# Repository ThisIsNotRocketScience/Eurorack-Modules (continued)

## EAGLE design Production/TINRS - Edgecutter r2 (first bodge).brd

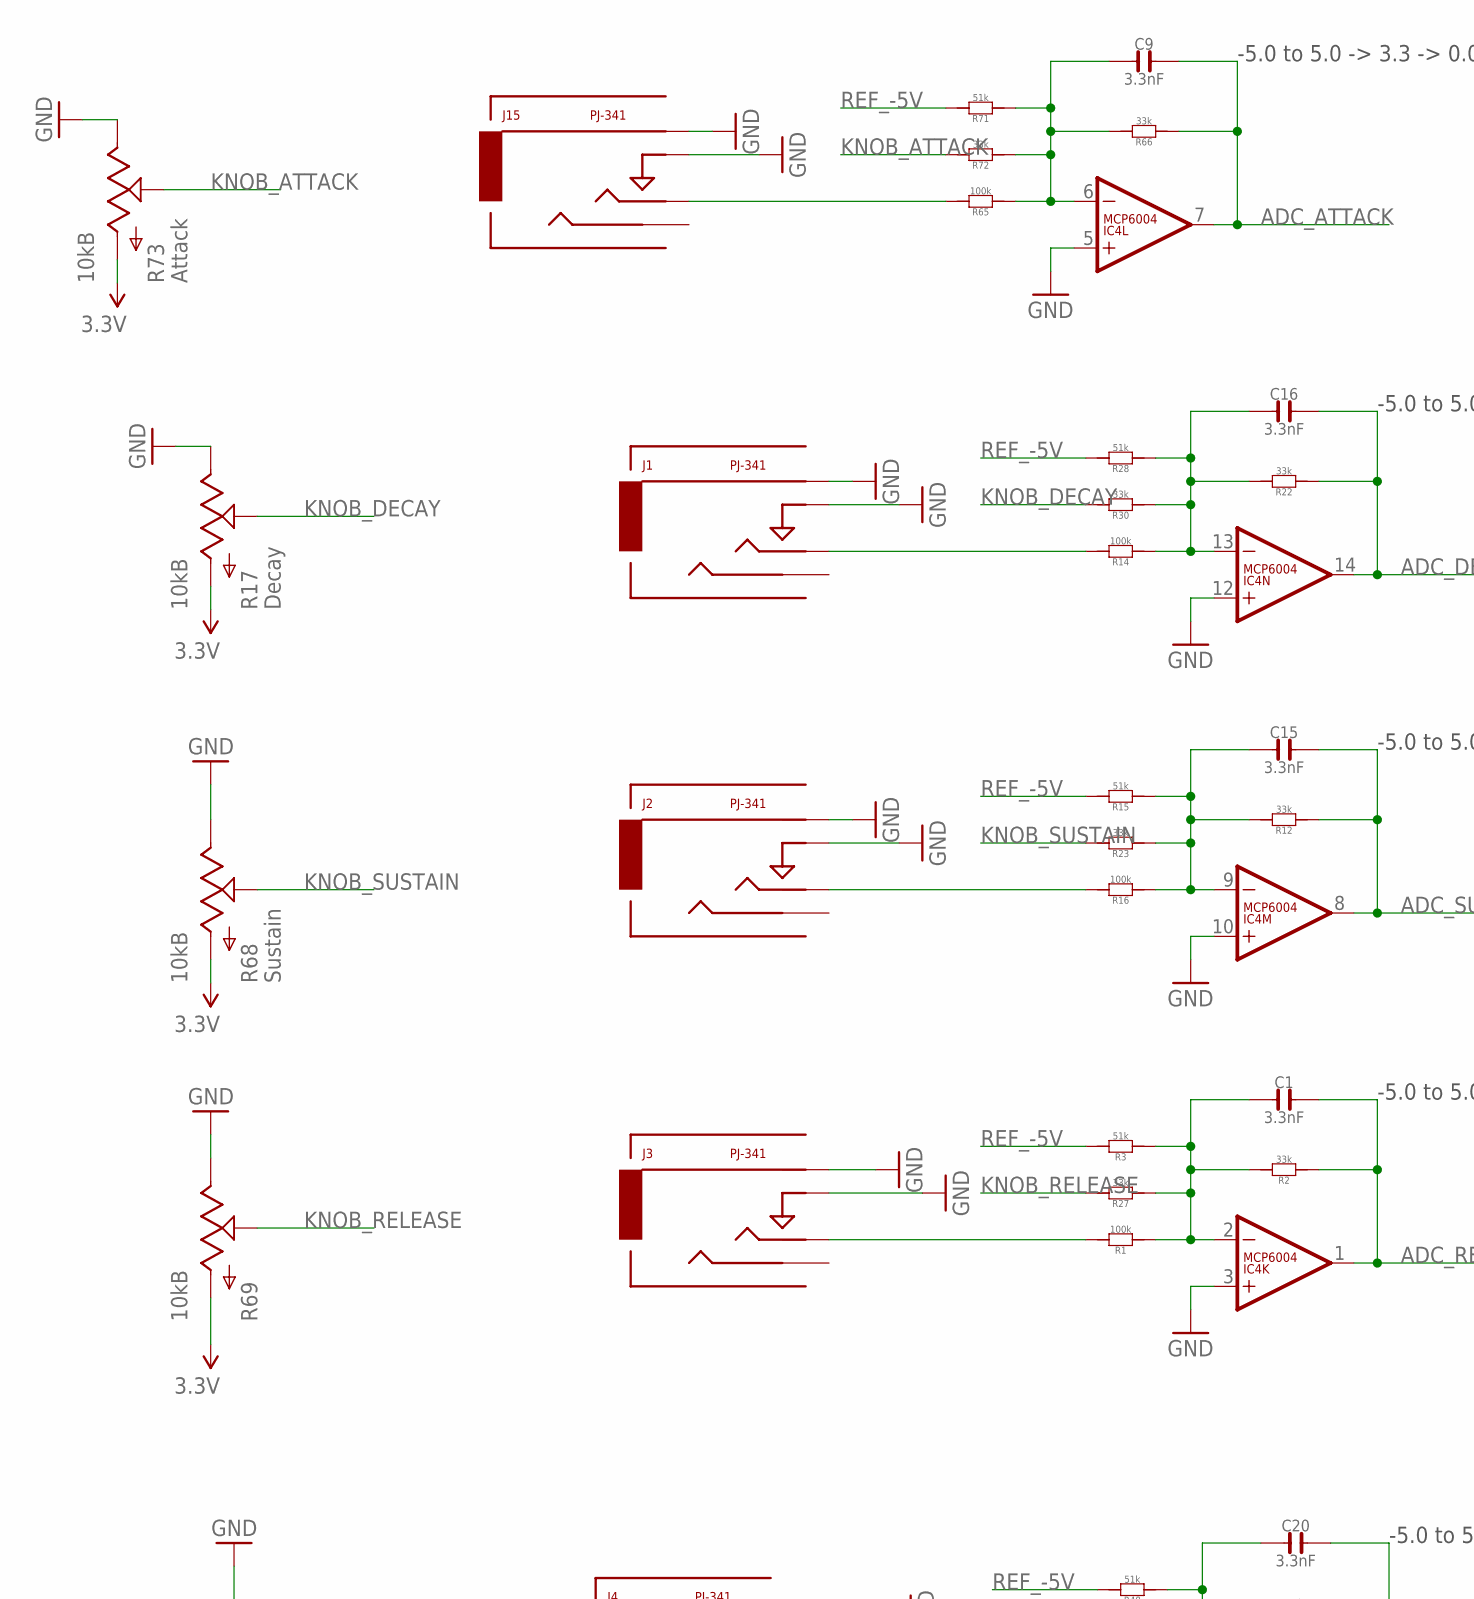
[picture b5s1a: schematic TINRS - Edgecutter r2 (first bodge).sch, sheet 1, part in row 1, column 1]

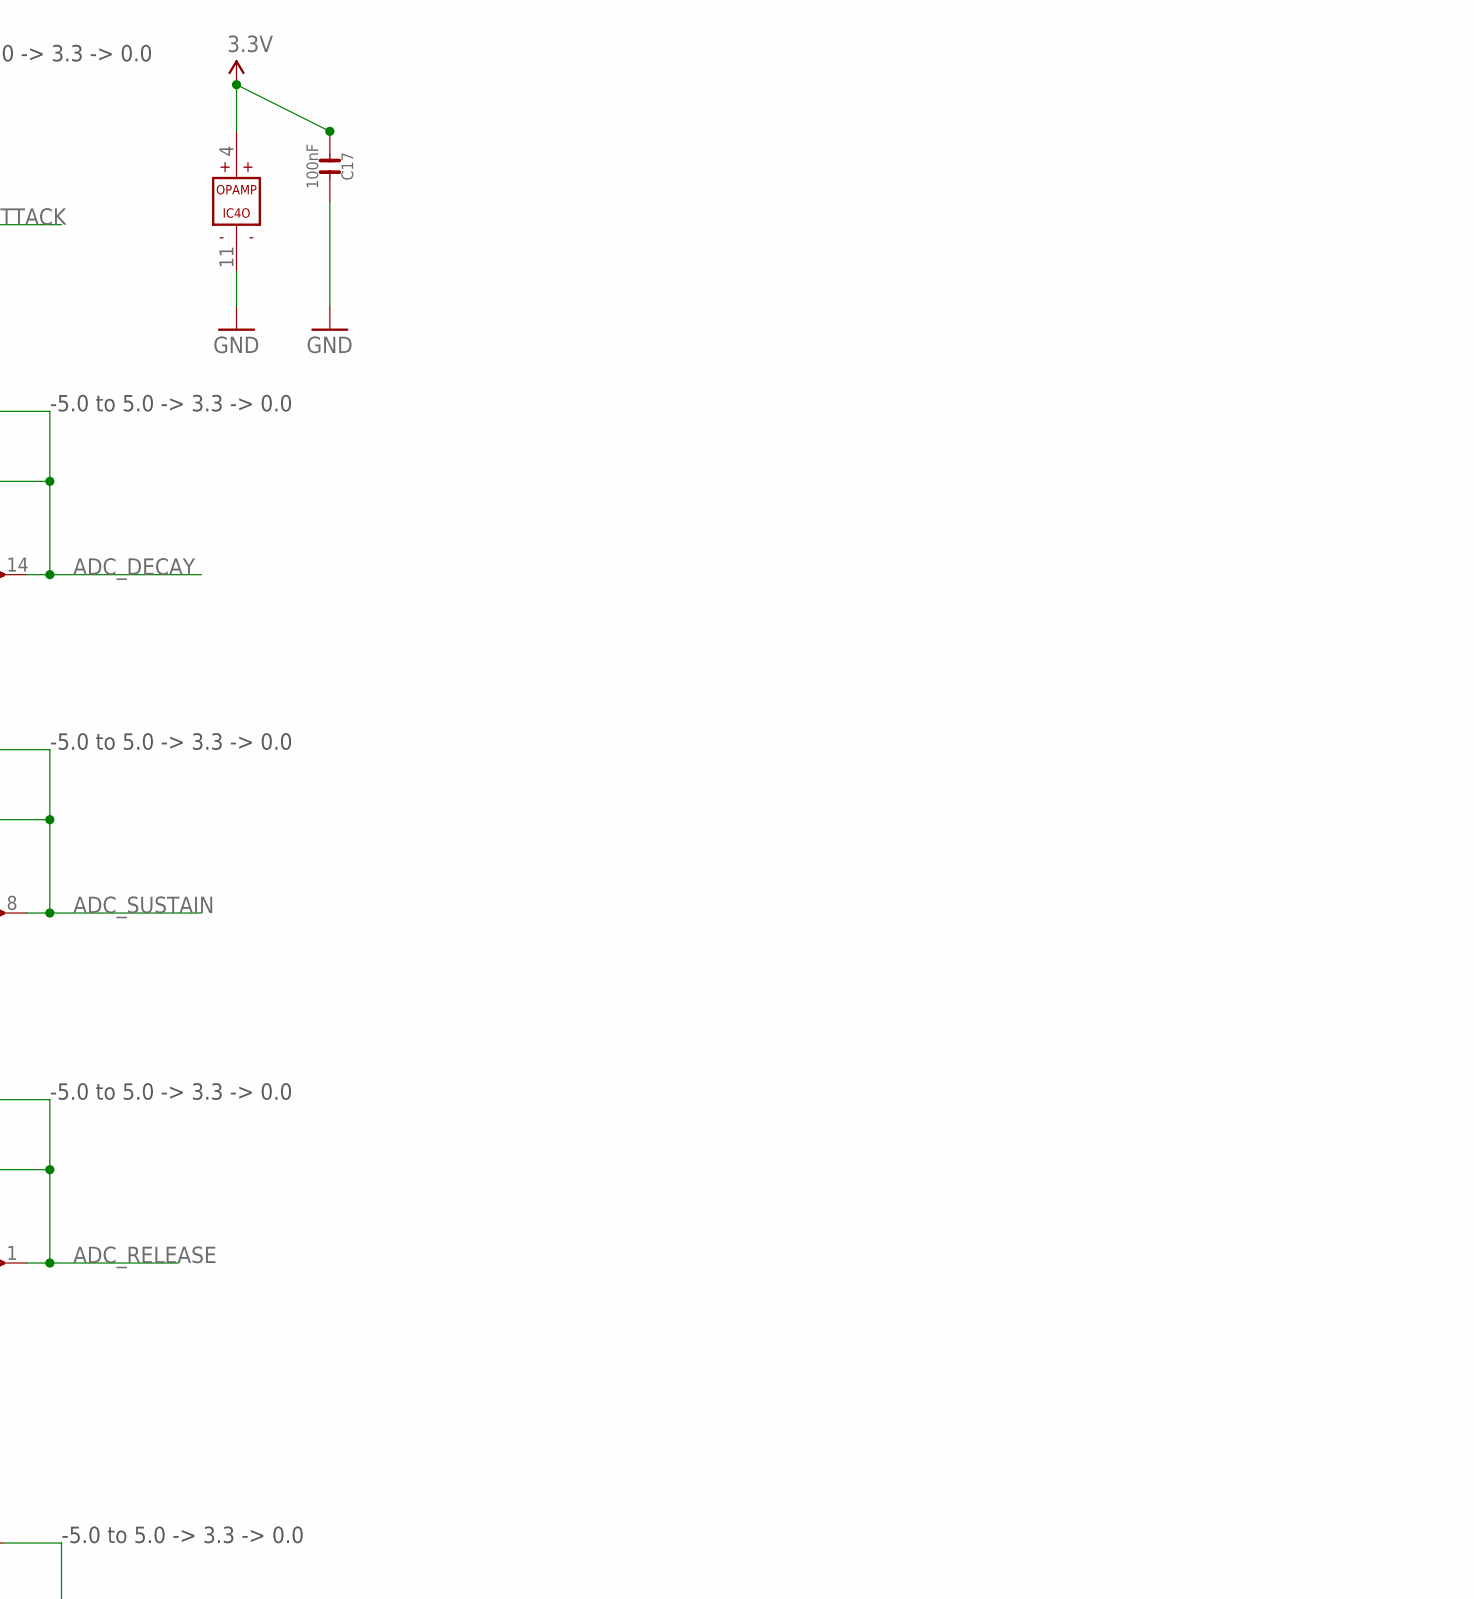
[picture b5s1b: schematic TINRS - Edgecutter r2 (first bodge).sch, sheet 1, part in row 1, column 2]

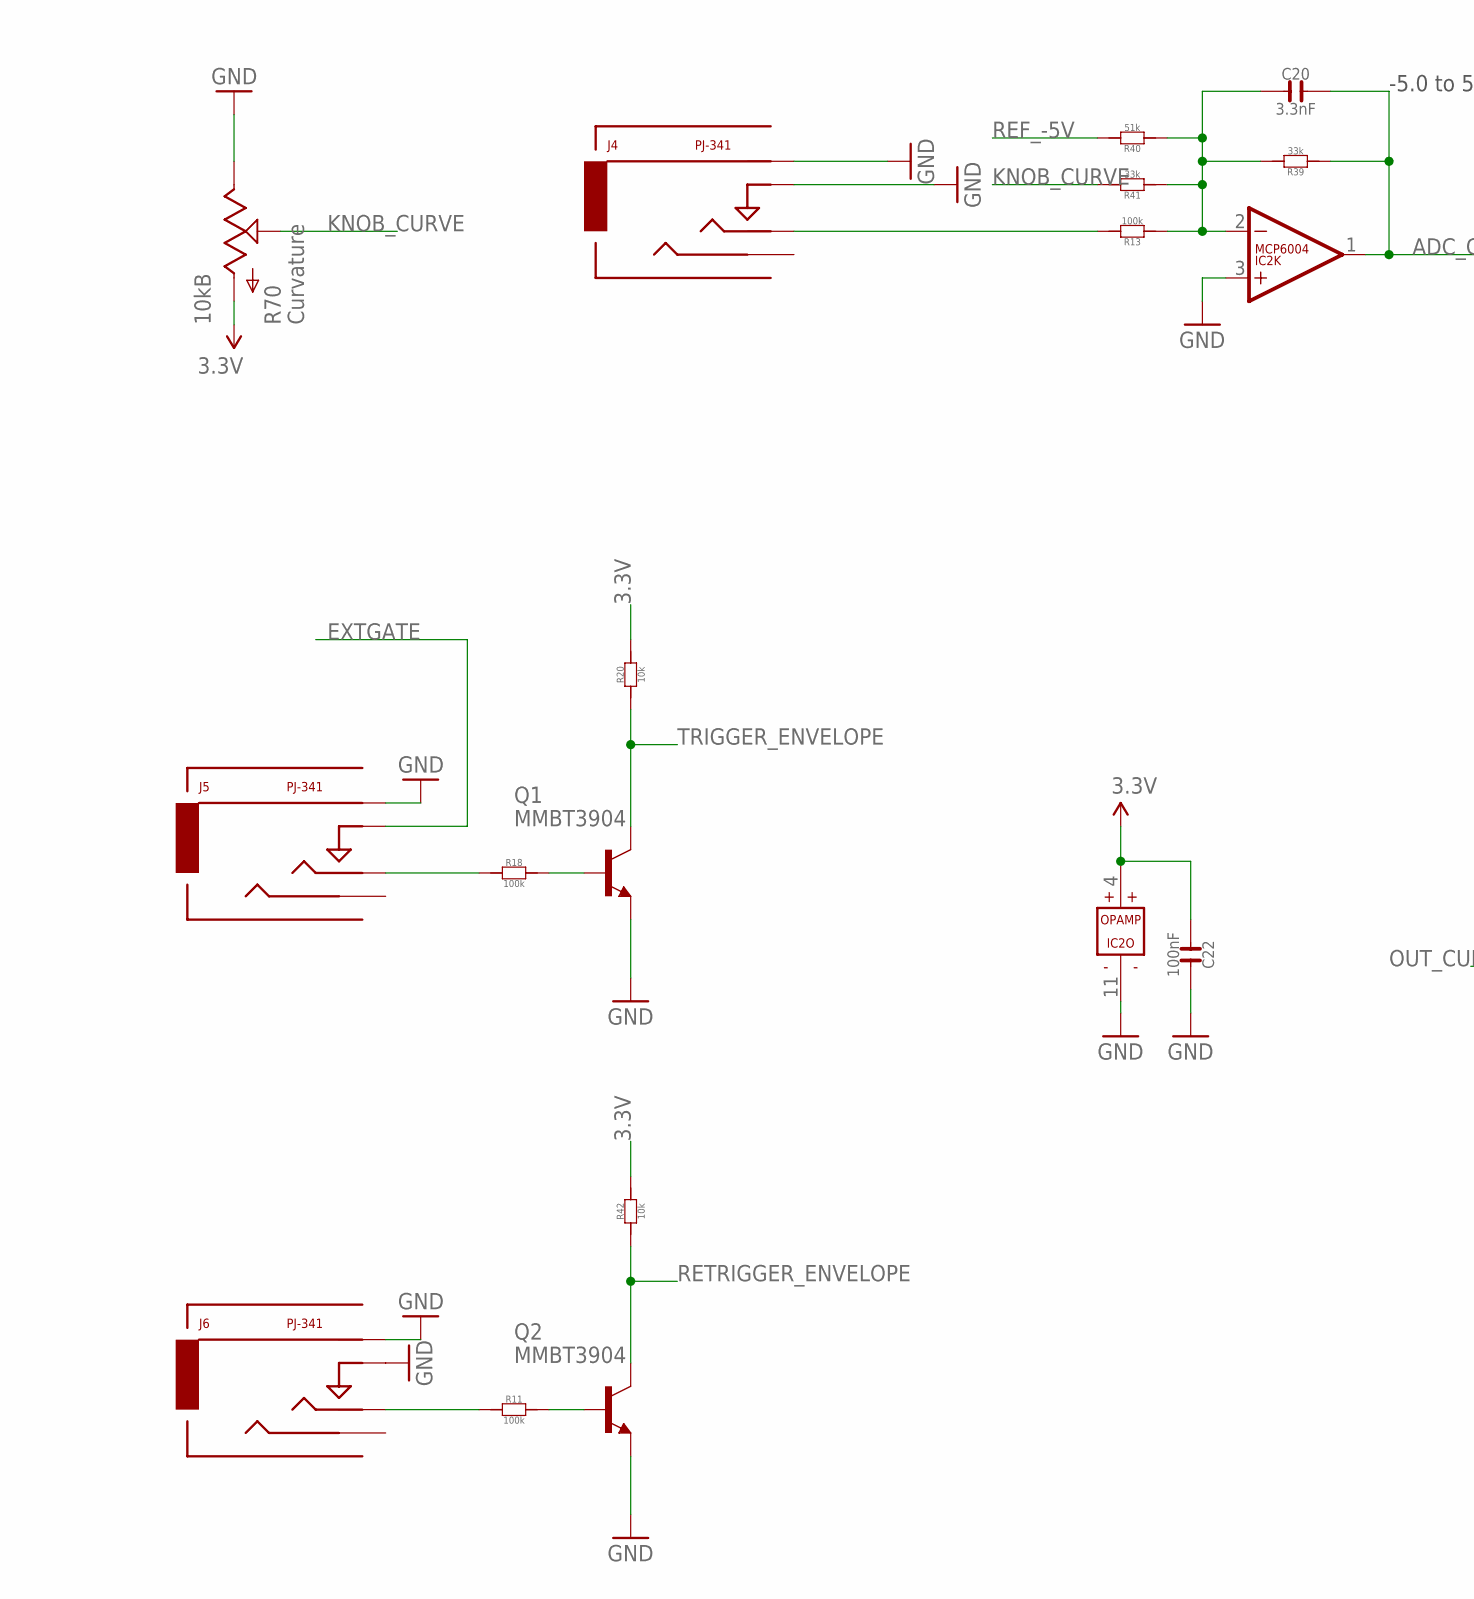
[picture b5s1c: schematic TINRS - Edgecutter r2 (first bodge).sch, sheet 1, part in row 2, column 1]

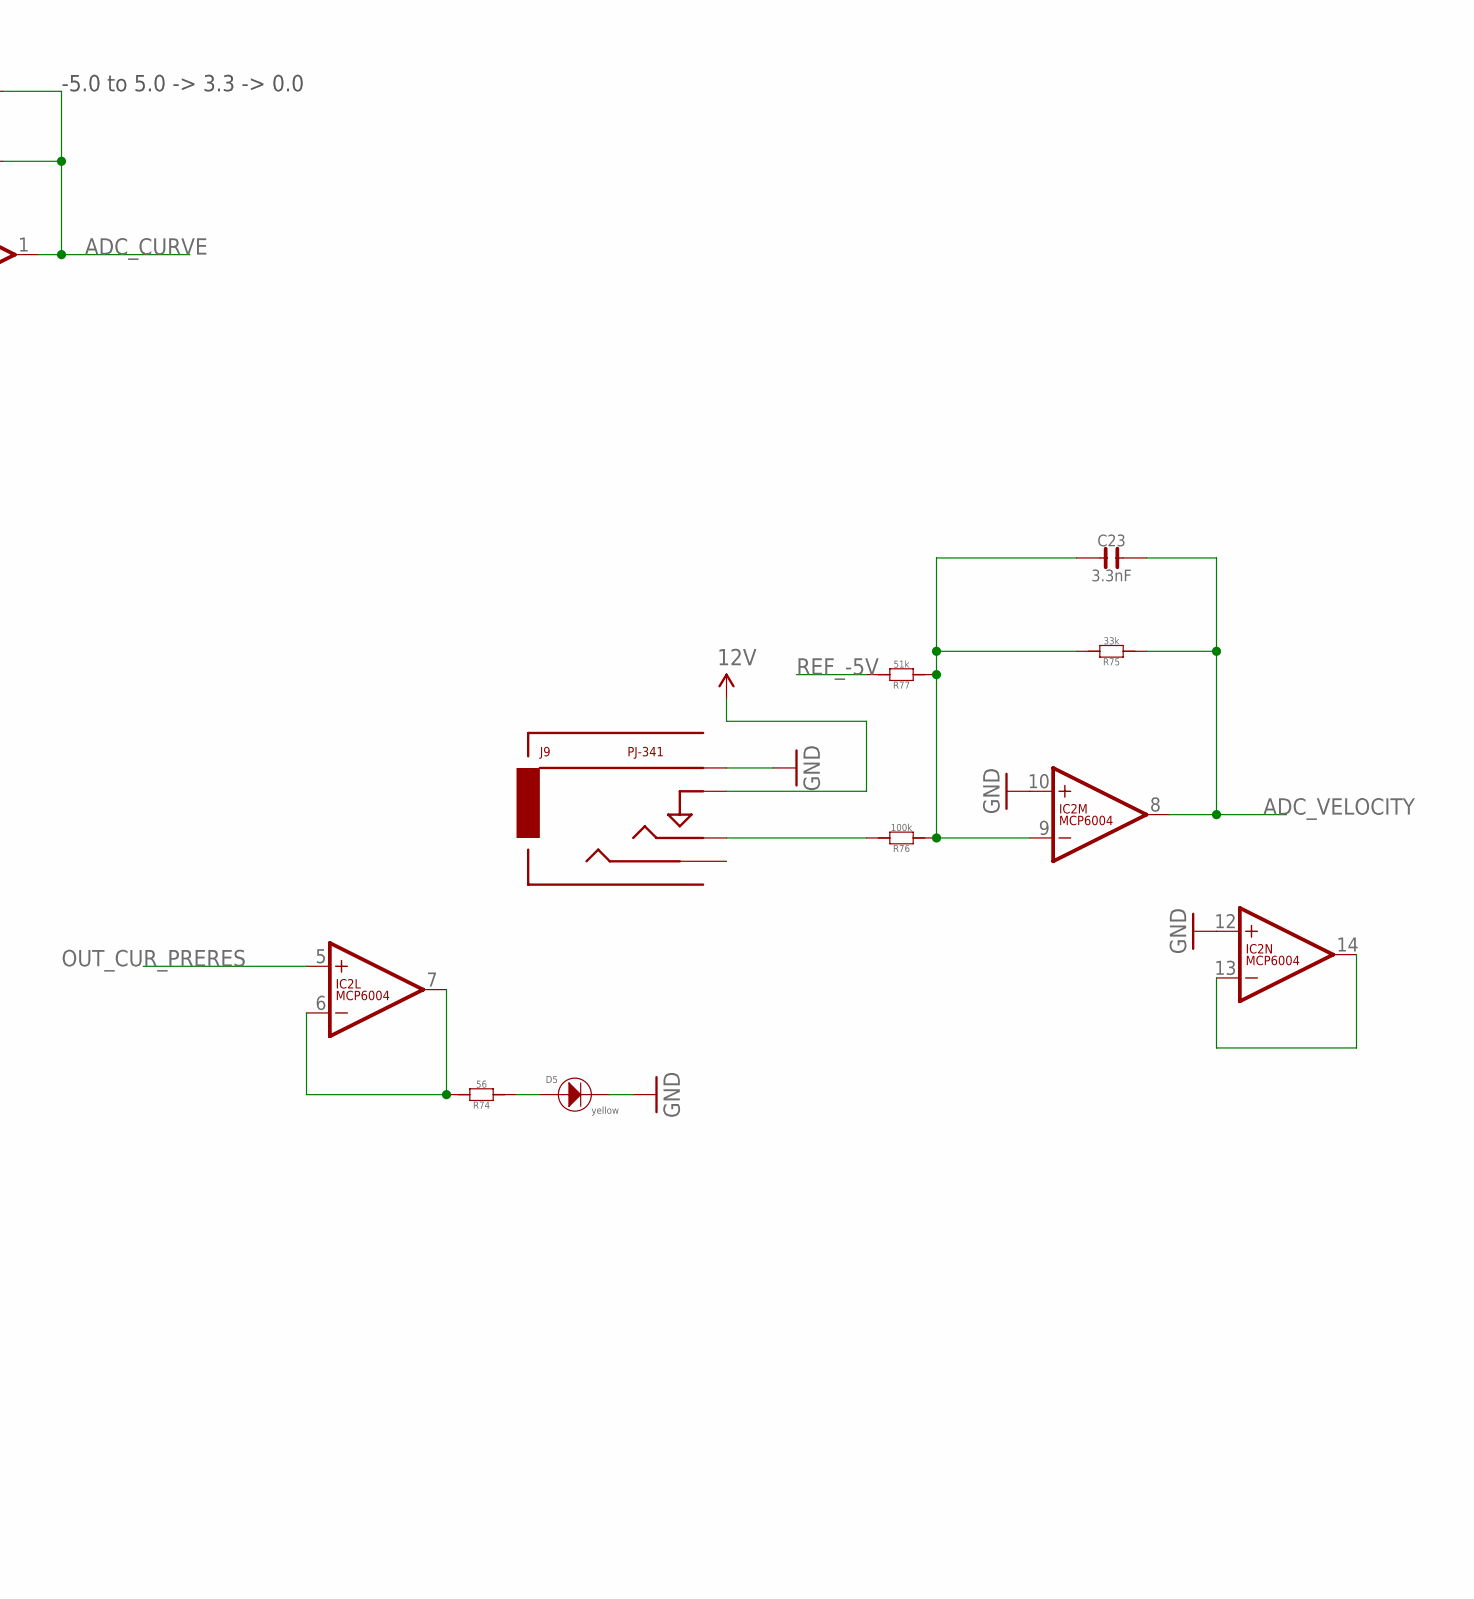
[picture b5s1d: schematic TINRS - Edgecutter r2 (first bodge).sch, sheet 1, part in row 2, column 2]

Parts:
C1, C9, C15, C16, C20, C23: 3.3nF; C0603
C17, C22: 100nF; C0603; MPN MC0603F104Z160CT
D5: yellow; 3MMLED
IC2, IC4: MCP6004; SO14; MPN MCP6004-I/SL.
J1, J2, J3, J4, J5, J6, J9, J15: PJ-341; 3.5MM-JACK-SWITCH-13MM-INPUT
Q1, Q2: MMBT3904; SOT23-BEC; MPN PMBT3904,215
R1, R11, R13, R14, R16, R18, R65, R76: 100k; R0603
R2, R12, R22, R23, R27, R30, R39, R41, R66, R72, R75: 33k; R0603
R3, R15, R28, R40, R71, R77: 51k; R0603
R17, R68, R69, R70, R73: 10kB; OG-POTS_ALPS_POT_VERTICAL
R20, R42: 10k; R0603
R74: 56; R0603

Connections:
3.3V: C17.1, C22.1, IC2.4 (V+), IC4.4 (V+), R17.P$3 (A), R20.2, R42.2, R68.P$3 (A), R69.P$3 (A), R70.P$3 (A), R73.P$3 (A); also elsewhere on the board
12V: J9.SWITCH@3 (SWITCH); also elsewhere on the board
ADC_ATTACK: C9.2, IC4.7 (OUT), R66.1; also elsewhere on the board
ADC_CURVE: C20.2, IC2.1 (OUT), R39.1; also elsewhere on the board
ADC_DECAY: C16.2, IC4.14 (OUT), R22.1; also elsewhere on the board
ADC_RELEASE: C1.2, IC4.1 (OUT), R2.1; also elsewhere on the board
ADC_SUSTAIN: C15.2, IC4.8 (OUT), R12.1; also elsewhere on the board
ADC_VELOCITY: C23.2, IC2.8 (OUT), R75.1; also elsewhere on the board
EXTGATE: J5.SWITCH@3 (SWITCH); also elsewhere on the board
GND: C17.2, C22.2, D5.-, IC2.3 (+IN), IC2.10 (+IN), IC2.11 (V-), IC2.12 (+IN), IC4.3 (+IN), IC4.5 (+IN), IC4.10 (+IN), IC4.11 (V-), IC4.12 (+IN), J1.RING@3 (RING), J1.SWITCH@3 (SWITCH), J2.RING@3 (RING), J2.SWITCH@3 (SWITCH), J3.RING@3 (RING), J3.SWITCH@3 (SWITCH), J4.RING@3 (RING), J4.SWITCH@3 (SWITCH), J5.RING@3 (RING), J6.RING@3 (RING), J6.SWITCH@3 (SWITCH), J9.RING@3 (RING), J15.RING@3 (RING), J15.SWITCH@3 (SWITCH), Q1.E, Q2.E, R17.P$1 (E), R68.P$1 (E), R69.P$1 (E), R70.P$1 (E), R73.P$1 (E); also elsewhere on the board
KNOB_ATTACK: R72.2, R73.P$2 (S)
KNOB_CURVE: R41.2, R70.P$2 (S)
KNOB_DECAY: R17.P$2 (S), R30.2
KNOB_RELEASE: R27.2, R69.P$2 (S)
KNOB_SUSTAIN: R23.2, R68.P$2 (S)
unnamed: J2.TIP@3 (TIP), R16.2
unnamed: C15.1, IC4.9 (-IN), R12.2, R15.1, R16.1, R23.1
unnamed: J3.TIP@3 (TIP), R1.2
unnamed: C1.1, IC4.2 (-IN), R1.1, R2.2, R3.1, R27.1
unnamed: J15.TIP@3 (TIP), R65.2
unnamed: J4.TIP@3 (TIP), R13.2
unnamed: Q1.B, R18.2
unnamed: J5.TIP@3 (TIP), R18.1
unnamed: IC2.6 (-IN), IC2.7 (OUT), R74.2
unnamed: C9.1, IC4.6 (-IN), R65.1, R66.2, R71.1, R72.1
unnamed: IC2.13 (-IN), IC2.14 (OUT)
unnamed: J1.TIP@3 (TIP), R14.2
unnamed: C16.1, IC4.13 (-IN), R14.1, R22.2, R28.1, R30.1
unnamed: Q2.B, R11.2
unnamed: C20.1, IC2.2 (-IN), R13.1, R39.2, R40.1, R41.1
unnamed: J6.TIP@3 (TIP), R11.1
unnamed: C23.1, IC2.9 (-IN), R75.2, R76.1, R77.1
unnamed: D5.+, R74.1
unnamed: J9.TIP@3 (TIP), R76.2
OUT_CUR_PRERES: IC2.5 (+IN); also elsewhere on the board
REF_-5V: R3.2, R15.2, R28.2, R40.2, R71.2, R77.2; also elsewhere on the board
RETRIGGER_ENVELOPE: Q2.C, R42.1; also elsewhere on the board
TRIGGER_ENVELOPE: Q1.C, R20.1; also elsewhere on the board

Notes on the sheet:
-5.0 to 5.0 -> 3.3 -> 0.0

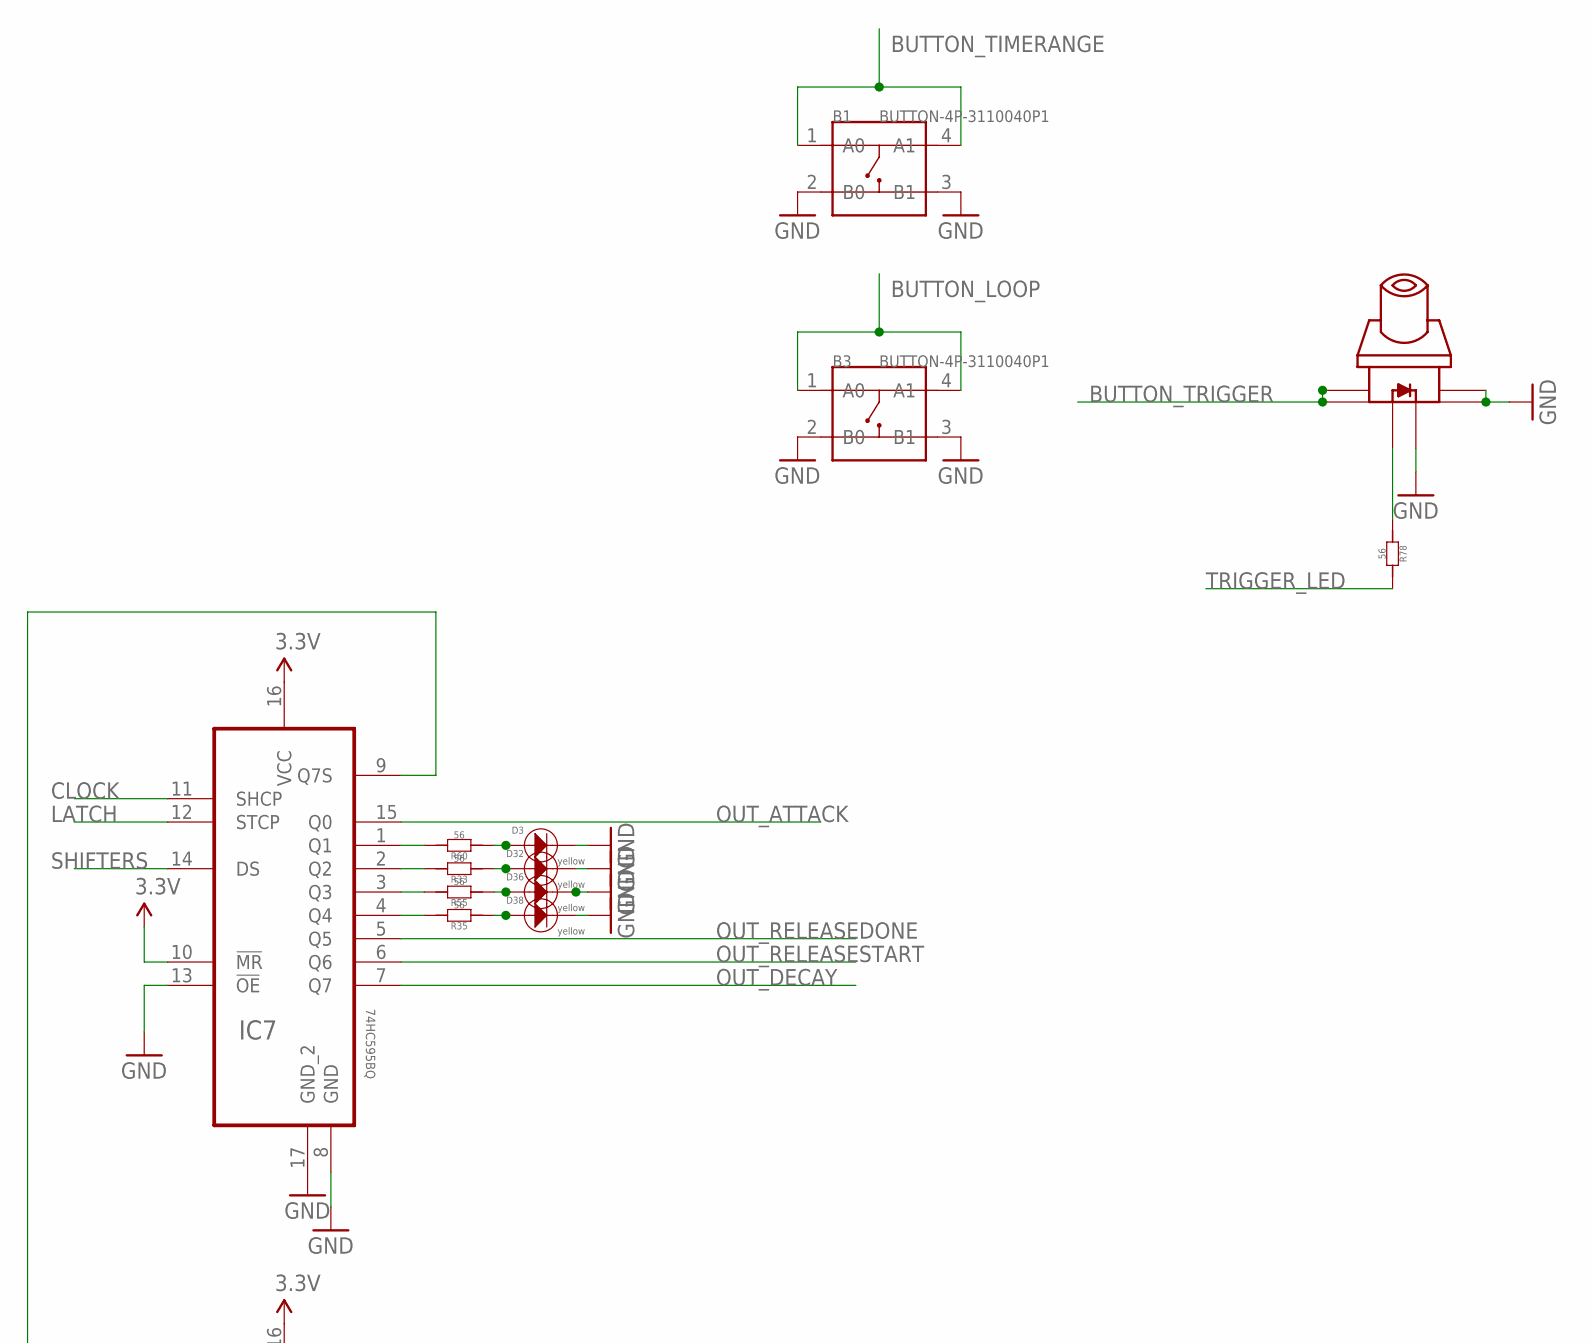
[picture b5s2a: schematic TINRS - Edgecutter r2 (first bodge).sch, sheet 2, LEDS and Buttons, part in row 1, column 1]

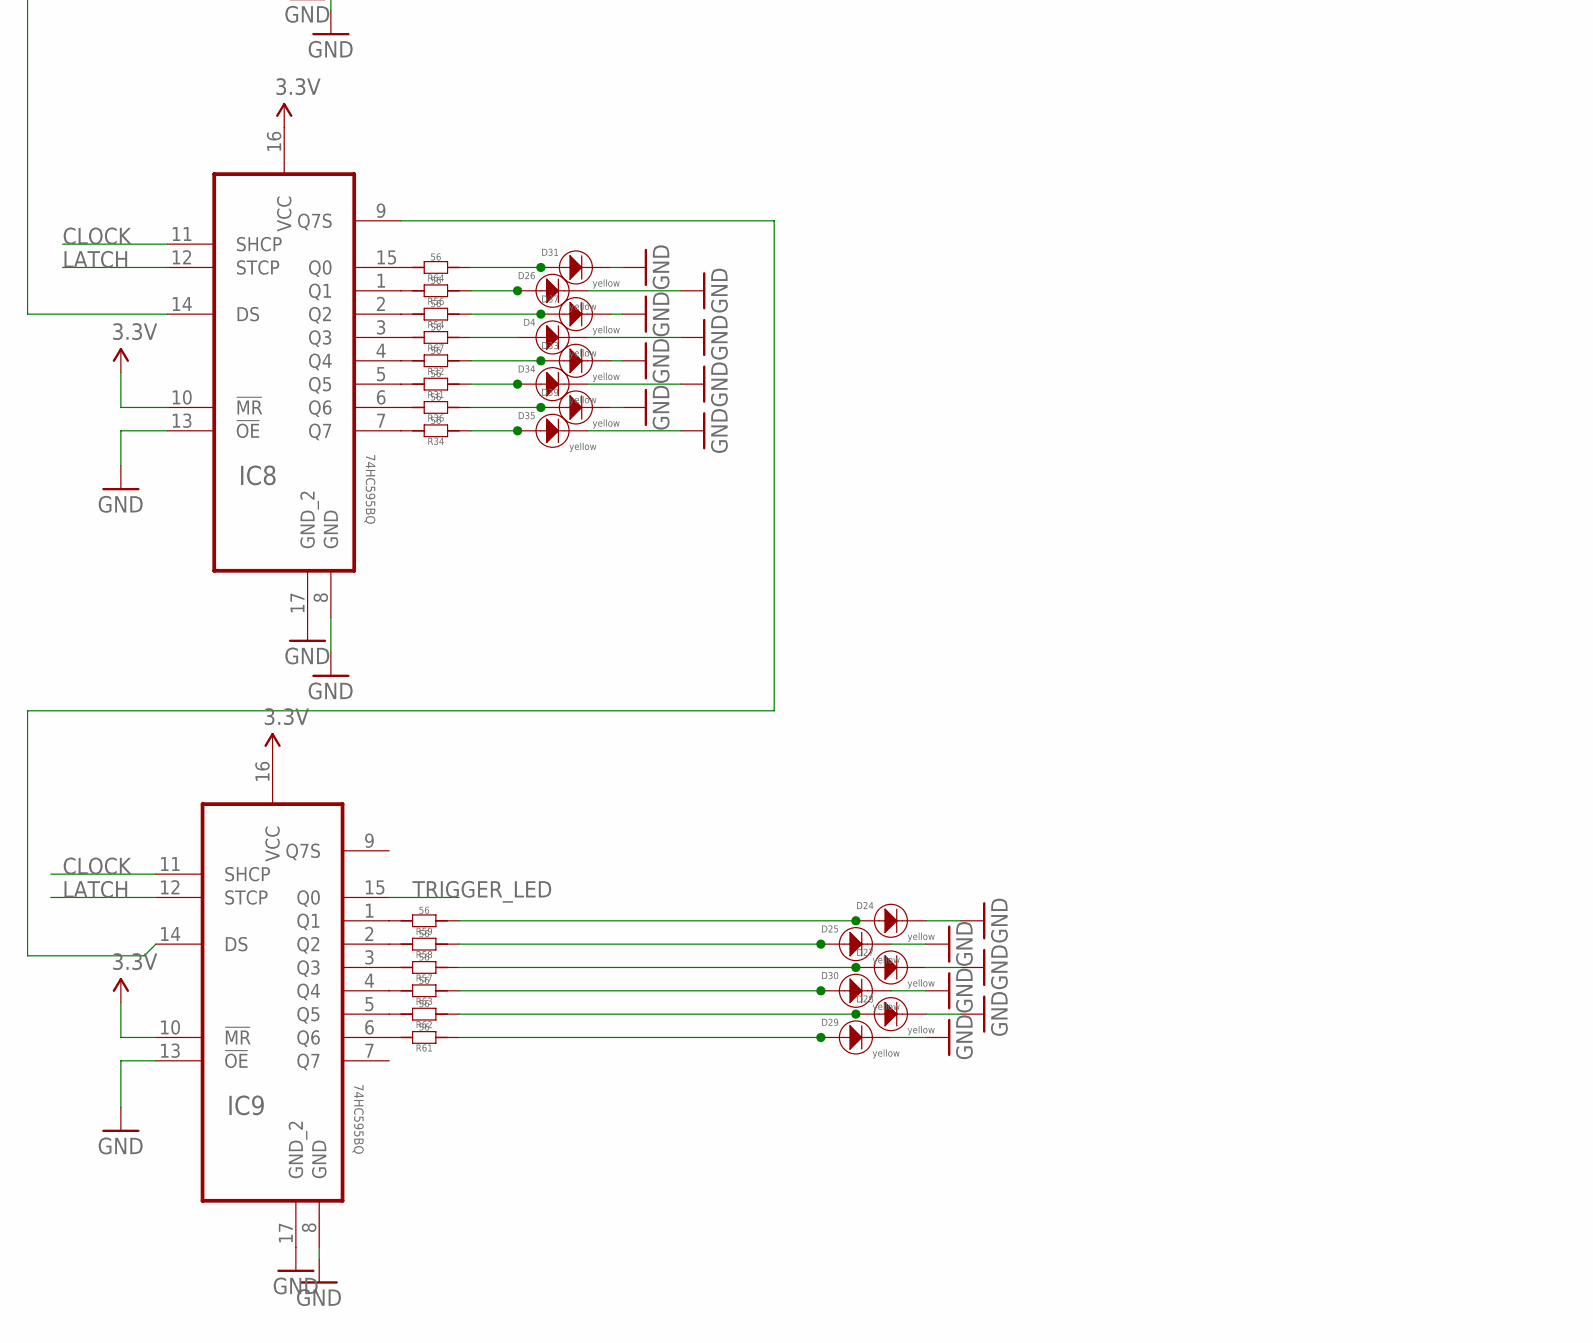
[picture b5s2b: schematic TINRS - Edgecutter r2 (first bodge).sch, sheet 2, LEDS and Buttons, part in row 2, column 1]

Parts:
B1, B3: BUTTON-4P-3110040P1; 4P-6.0X6.0X5.0H
D3, D4, D24, D25, D26, D27, D28, D29, D30, D31, D32, D33, D34, D35, D36, D37, D38, D39: yellow; 3MMLED
IC7, IC8, IC9: 74HC595BQ; QFN50P250X350X100-17N
R31, R32, R33, R34, R35, R36, R54, R55, R56, R57, R58, R59, R60, R61, R62, R63, R64, R67, R78: 56; R0603
U$2: SWITCH_W_LED_PB6149L-X-102YELLOW; PB6149L

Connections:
3.3V: IC7.10 (!MR), IC7.16 (VCC), IC8.10 (!MR), IC8.16 (VCC), IC9.10 (!MR), IC9.16 (VCC); also elsewhere on the board
BUTTON_LOOP: B3.1 (A0), B3.4 (A1); also elsewhere on the board
BUTTON_TIMERANGE: B1.1 (A0), B1.4 (A1); also elsewhere on the board
BUTTON_TRIGGER: U$2.1, U$2.2; also elsewhere on the board
CLOCK: IC7.11 (SHCP), IC8.11 (SHCP), IC9.11 (SHCP); also elsewhere on the board
GND: B1.2 (B0), B1.3 (B1), B3.2 (B0), B3.3 (B1), D3.-, D4.-, D24.-, D25.-, D26.-, D27.-, D28.-, D29.-, D30.-, D31.-, D32.-, D33.-, D34.-, D35.-, D36.-, D37.-, D38.-, D39.-, IC7.8 (GND), IC7.13 (!OE), IC7.17 (GND_2), IC8.8 (GND), IC8.13 (!OE), IC8.17 (GND_2), IC9.8 (GND), IC9.13 (!OE), IC9.17 (GND_2), U$2.3, U$2.4, U$2.LEDNEG (NEG); also elsewhere on the board
LATCH: IC7.12 (STCP), IC8.12 (STCP), IC9.12 (STCP); also elsewhere on the board
unnamed: R78.1, U$2.LEDPOS (POS)
unnamed: IC8.7 (Q7), R34.2
unnamed: IC8.15 (Q0), R64.2
unnamed: D28.+, R62.1
unnamed: D4.+, R67.1
unnamed: IC7.1 (Q1), R60.2
unnamed: D29.+, R61.1
unnamed: IC7.2 (Q2), R33.2
unnamed: IC7.3 (Q3), R55.2
unnamed: IC7.4 (Q4), R35.2
unnamed: IC8.1 (Q1), R56.2
unnamed: IC8.2 (Q2), R54.2
unnamed: IC8.3 (Q3), R67.2
unnamed: IC8.4 (Q4), R32.2
unnamed: IC8.5 (Q5), R31.2
unnamed: IC8.6 (Q6), R36.2
unnamed: IC9.1 (Q1), R59.2
unnamed: IC9.2 (Q2), R58.2
unnamed: D3.+, R60.1
unnamed: IC9.3 (Q3), R57.2
unnamed: IC9.4 (Q4), R63.2
unnamed: IC9.5 (Q5), R62.2
unnamed: IC9.6 (Q6), R61.2
unnamed: D27.+, R57.1
unnamed: D26.+, R56.1
unnamed: D25.+, R58.1
unnamed: D24.+, R59.1
unnamed: D30.+, R63.1
unnamed: D31.+, R64.1
unnamed: D32.+, R33.1
unnamed: D33.+, R32.1
unnamed: D34.+, R31.1
unnamed: D35.+, R34.1
unnamed: D36.+, R55.1
unnamed: D37.+, R54.1
unnamed: D38.+, R35.1
unnamed: D39.+, R36.1
OUT_ATTACK: IC7.15 (Q0); also elsewhere on the board
OUT_DECAY: IC7.7 (Q7); also elsewhere on the board
OUT_RELEASEDONE: IC7.5 (Q5); also elsewhere on the board
OUT_RELEASESTART: IC7.6 (Q6); also elsewhere on the board
SHIFTER1TO2: IC7.9 (Q7S), IC8.14 (DS)
SHIFTER2TO3: IC8.9 (Q7S), IC9.14 (DS)
SHIFTERS: IC7.14 (DS); also elsewhere on the board
TRIGGER_LED: IC9.15 (Q0), R78.2

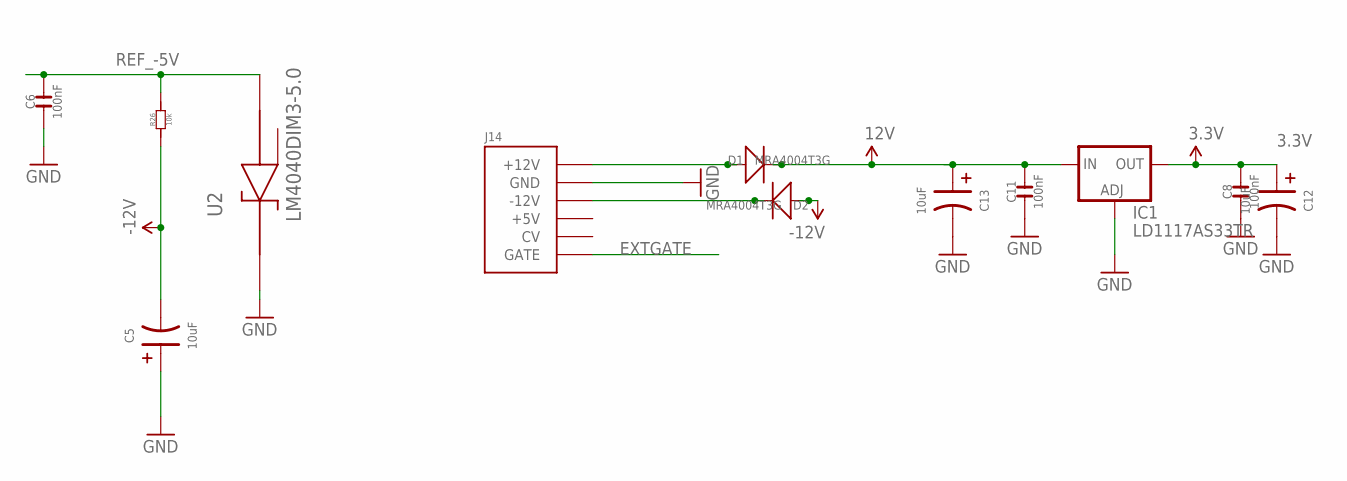
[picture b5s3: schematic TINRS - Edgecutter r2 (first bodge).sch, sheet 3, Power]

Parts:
C5, C12, C13: 10uF; CASE-A_3216; MPN TAJB106K020RNJ
C6: 100nF; C0603; MPN 06035C104KAT2A
C8, C11: 100nF; C0603; MPN MC0603F104Z160CT
D1, D2: MRA4004T3G; DO-214AC; MPN US1G-E3/5AT
IC1: LD1117AS33TR; SOT223; MPN LD1117AS33TR
J14: POWERSMT; 2X08_SMT_HEADER
R26: 10k; R0603
U2: LM4040DIM3-5.0; SOT95P237X112-3N

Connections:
3.3V: C8.2, C12.+ (1), IC1.2 (OUT), IC1.4 (OUT); also elsewhere on the board
12V: C11.2, C13.+ (1), D1.2 (-), IC1.3 (IN); also elsewhere on the board
-12V: C5.- (2), D2.1 (+), R26.1; also elsewhere on the board
EXTGATE: J14.15 (GATE), J14.16 (GATE); also elsewhere on the board
GND: C5.+ (1), C6.1, C8.1, C11.1, C12.- (2), C13.- (2), IC1.1 (ADJ), J14.3 (GND), J14.4 (GND), J14.5 (GND), J14.6 (GND), J14.7 (GND), J14.8 (GND), U2.1 (CATHODE); also elsewhere on the board
unnamed: D1.1 (+), J14.9 (+12V), J14.10 (+12V)
unnamed: D2.2 (-), J14.1 (-12V), J14.2 (-12V)
REF_-5V: C6.2, R26.2, U2.2 (ANODE); also elsewhere on the board

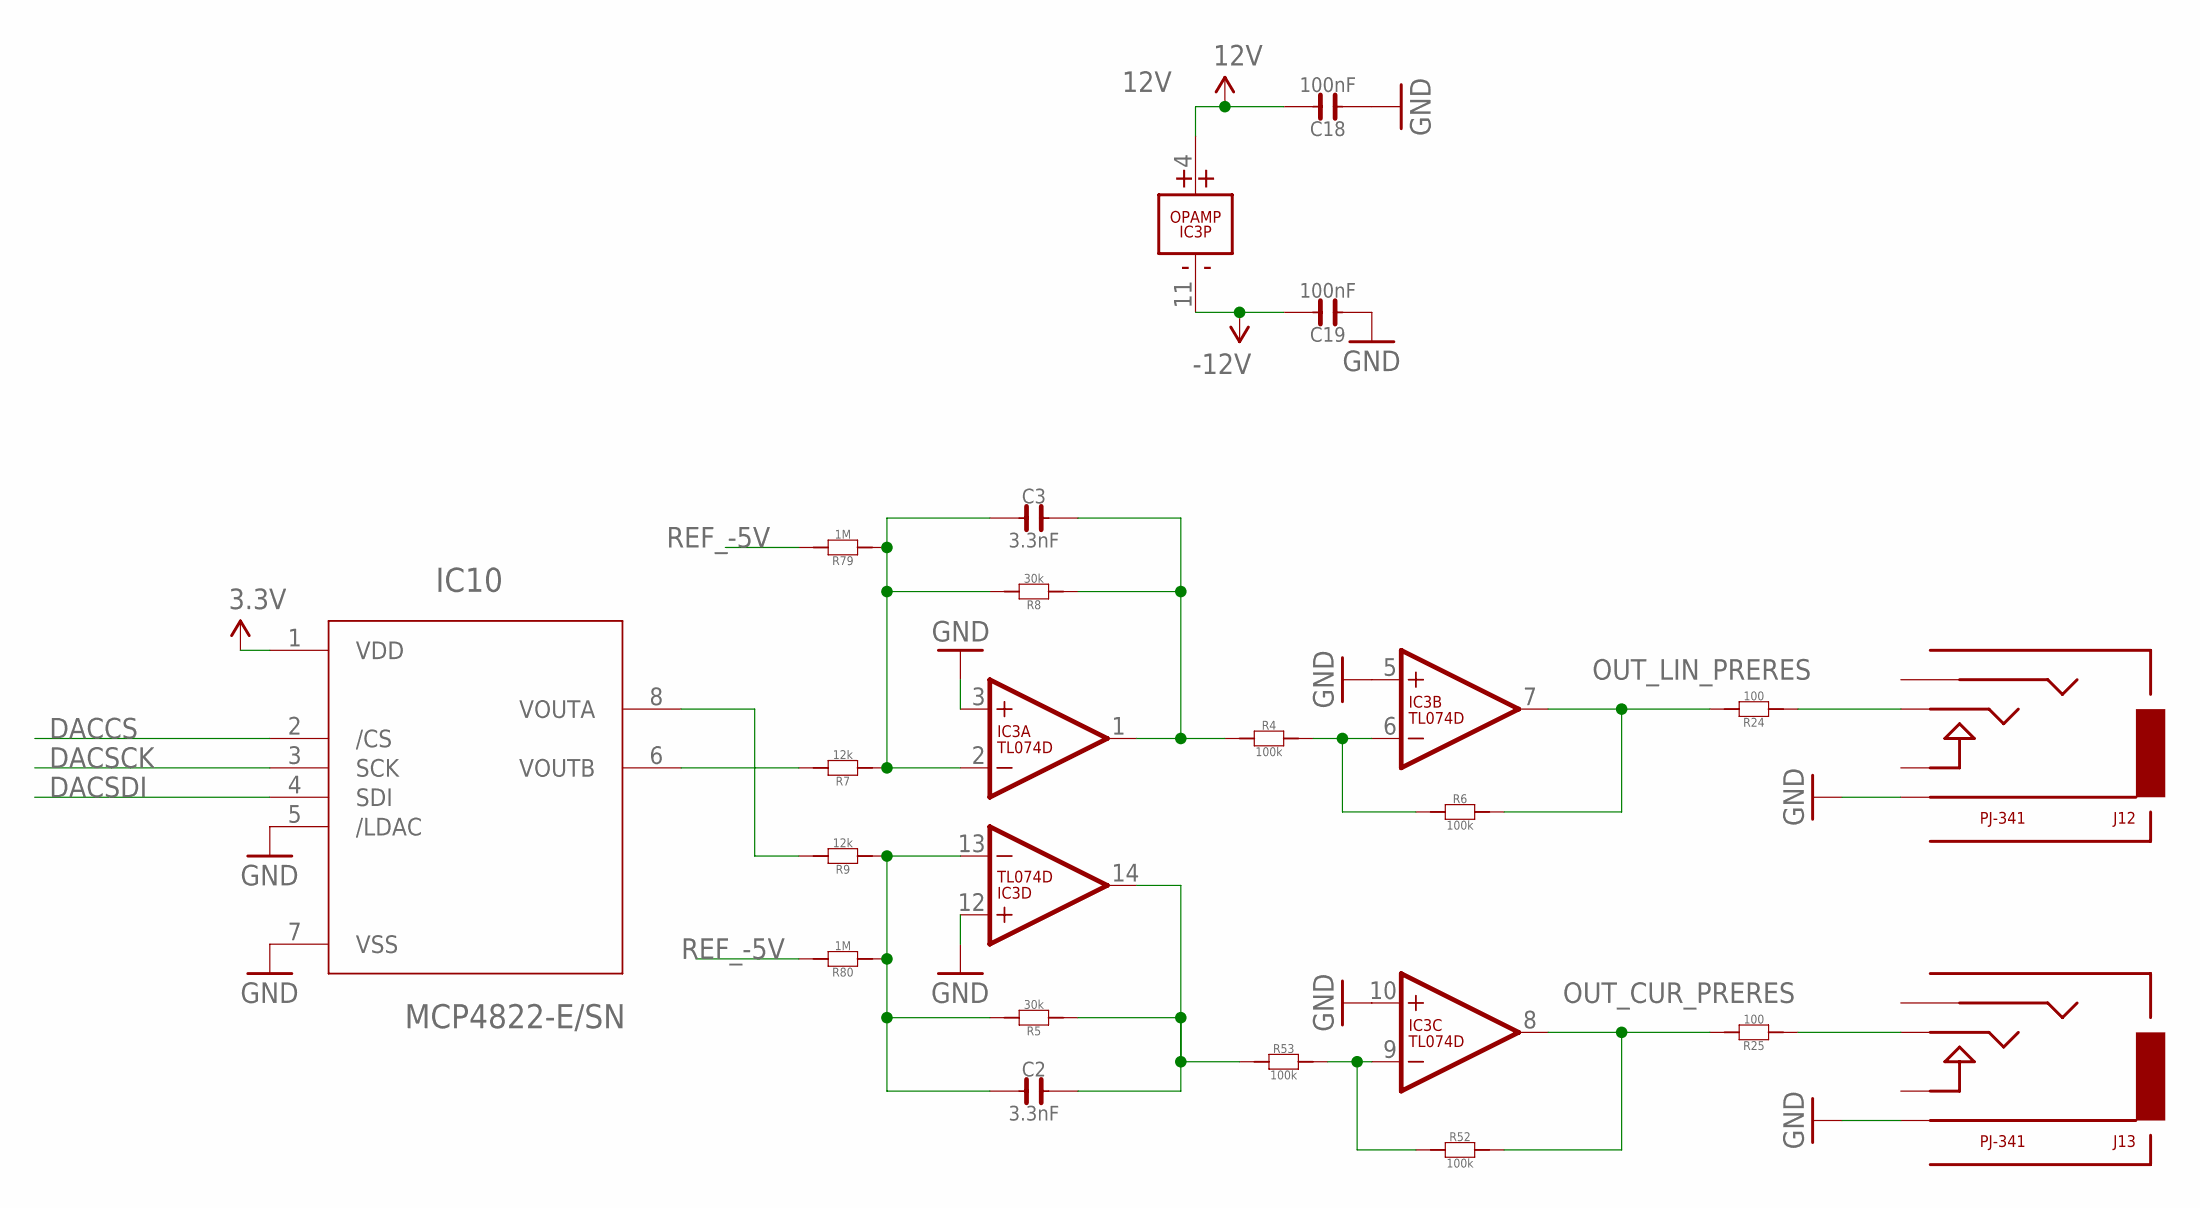
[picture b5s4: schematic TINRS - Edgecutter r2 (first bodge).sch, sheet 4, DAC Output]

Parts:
C2, C3: 3.3nF; C0603
C18, C19: 100nF; C0603; MPN MC0603F104Z160CT
IC3: TL074D; SO14; MPN TL074CD
IC10: MCP4822-E/SN; SOIC8-N_MC
J12, J13: PJ-341; 3.5MM-JACK-SWITCH-13MM-OUTPUT
R4, R6, R52, R53: 100k; R0603
R5, R8: 30k; R0603
R7, R9: 12k; R0603
R24, R25: 100; R0603
R79, R80: 1M; R0603

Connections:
3.3V: IC10.1 (VDD); also elsewhere on the board
12V: C18.2, IC3.4 (V+); also elsewhere on the board
-12V: C19.2, IC3.11 (V-); also elsewhere on the board
DACA_INPUTSUMMER: C2.1, IC3.13 (-IN), R5.2, R9.1, R80.1
DACB_INPUTSUMMER: C3.1, IC3.2 (-IN), R7.1, R8.2, R79.1
DACCS: IC10.2 (/CS); also elsewhere on the board
DACSCK: IC10.3 (SCK); also elsewhere on the board
DACSDI: IC10.4 (SDI); also elsewhere on the board
GND: C18.1, C19.1, IC3.3 (+IN), IC3.5 (+IN), IC3.10 (+IN), IC3.12 (+IN), IC10.5 (/LDAC), IC10.7 (VSS), J12.RING@3 (RING), J13.RING@3 (RING); also elsewhere on the board
unnamed: IC3.6 (-IN), R4.2, R6.1
unnamed: IC10.8 (VOUTA), R9.2
unnamed: IC10.6 (VOUTB), R7.2
unnamed: IC3.9 (-IN), R52.1, R53.2
unnamed: C3.2, IC3.1 (OUT), R4.1, R8.1
unnamed: J13.TIP@3 (TIP), R25.1
unnamed: J12.TIP@3 (TIP), R24.1
unnamed: C2.2, IC3.14 (OUT), R5.1, R53.1
OUT_CUR_PRERES: IC3.8 (OUT), R25.2, R52.2; also elsewhere on the board
OUT_LIN_PRERES: IC3.7 (OUT), R6.2, R24.2
REF_-5V: R79.2, R80.2; also elsewhere on the board
